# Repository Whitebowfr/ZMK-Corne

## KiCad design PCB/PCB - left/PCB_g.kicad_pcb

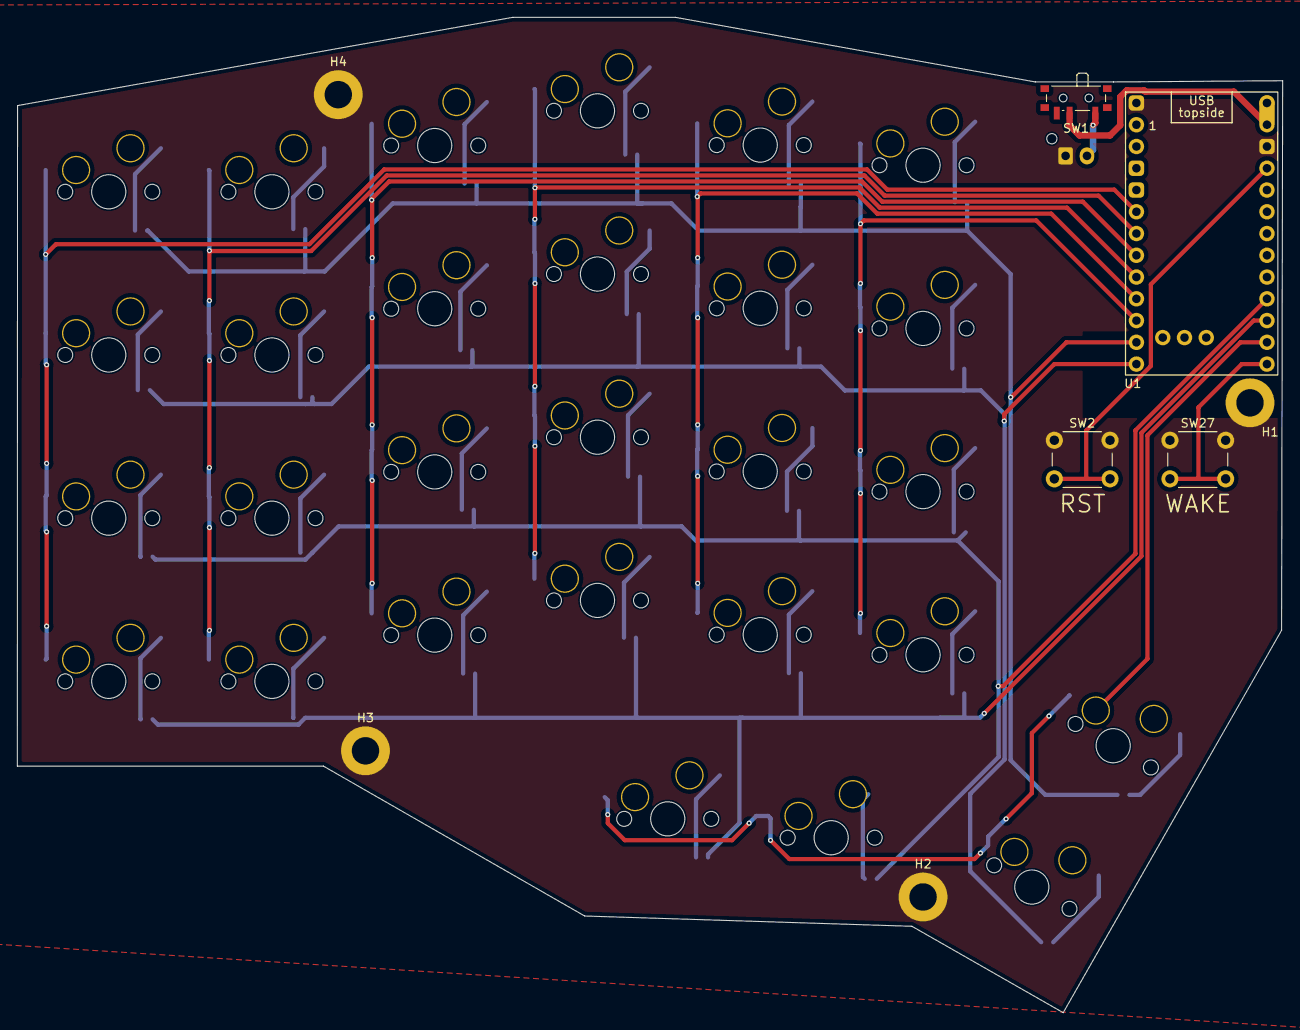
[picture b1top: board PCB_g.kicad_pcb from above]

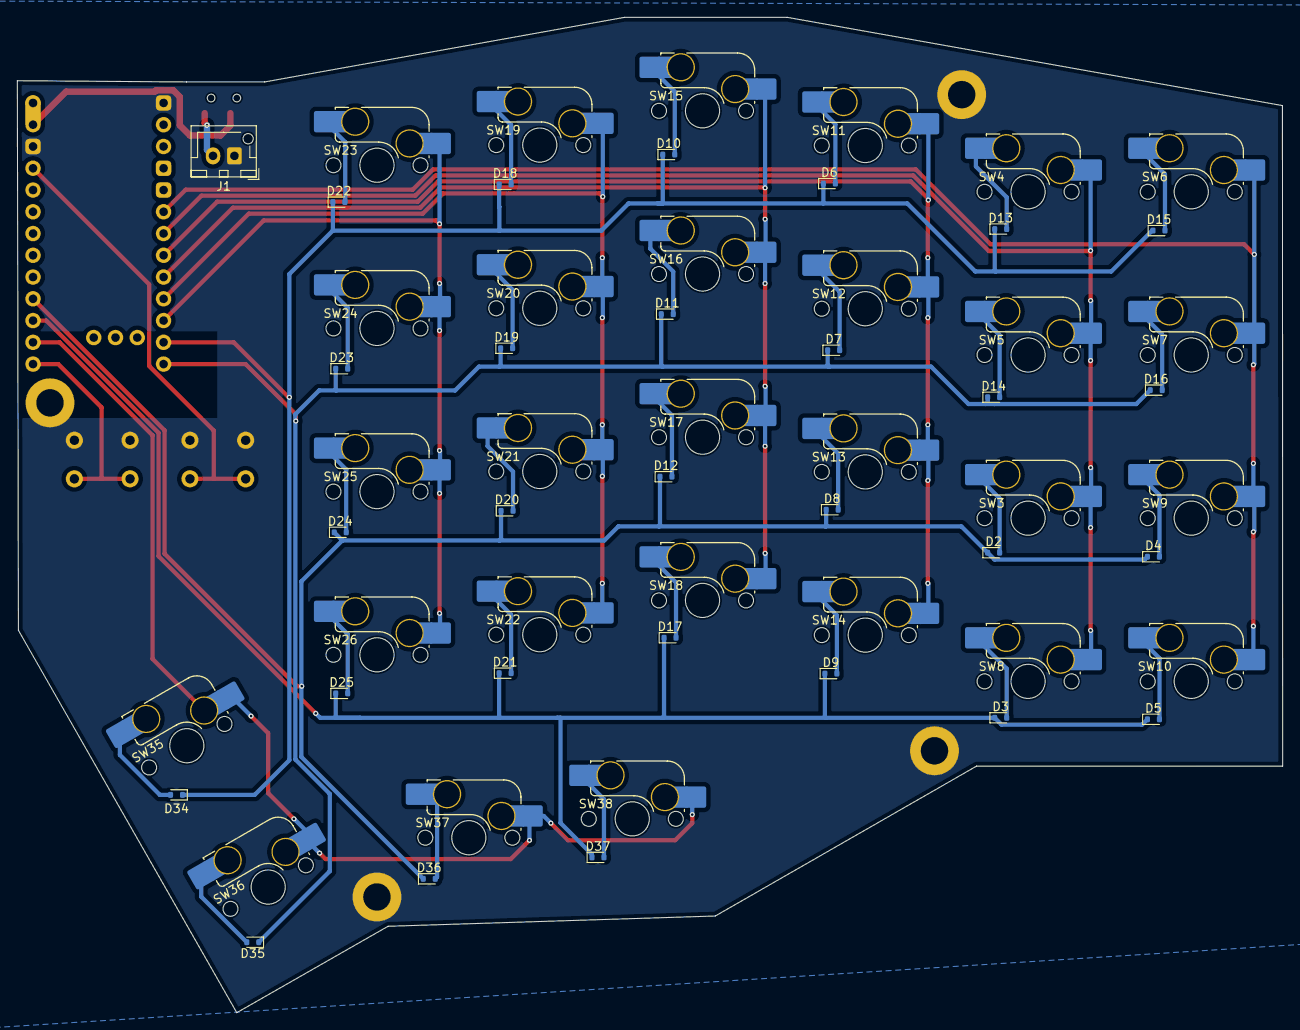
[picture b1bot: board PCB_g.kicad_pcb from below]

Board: 2 copper layers, 147.7 x 116.2 mm, 65 parts (57 on the bottom side), 44 nets.

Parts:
D2, D3, D4, D5, D6, D7, D8, D9, D10, D11, D12, D13, D14, D15, D16, D17, D18, D19, D20, D21, D22, D23, D24, D25, D34, D35, D36, D37: 1N4148WT; D_SOD-523
H1, H2, H3, H4: MountingHole_Pad; MountingHole_3.2mm_M3_ISO7380_Pad
J1: Conn_01x02; JST_XH_B2B-XH-AM_1x02_P2.50mm_Vertical
SW1: SW_SPDT; SW_SPDT_PCM12
SW2, SW27: SW_Push; SW_PUSH_6mm_H5mm
SW3, SW4, SW5, SW6, SW7, SW8, SW9, SW10, SW11, SW12, SW13, SW14, SW15, SW16, SW17, SW18, SW19, SW20, SW21, SW22, SW23, SW24, SW25, SW26, SW35, SW36, SW37, SW38: MX_SW_HS; SW_MX_HS_CPG151101S11_1u
U1: SuperMini nRF52840; SuperMini_nRF52840_AH_USBup

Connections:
+BATT: J1.2, SW1.1 (A)
GND: H1.1, H2.1, H3.1, H4.1, J1.1, SW2.1, SW27.1, U1.14 (GND), U1.28 (GND)
unnamed: D2.2 (A), SW3.2
unnamed: D3.2 (A), SW8.2
unnamed: D4.2 (A), SW9.2
unnamed: D5.2 (A), SW10.2
unnamed: D6.2 (A), SW11.2
unnamed: D7.2 (A), SW12.2
unnamed: D8.2 (A), SW13.2
unnamed: D9.2 (A), SW14.2
unnamed: D10.2 (A), SW15.2
unnamed: D11.2 (A), SW16.2
unnamed: D12.2 (A), SW17.2
unnamed: D13.2 (A), SW4.2
unnamed: D14.2 (A), SW5.2
unnamed: D15.2 (A), SW6.2
unnamed: D16.2 (A), SW7.2
unnamed: D17.2 (A), SW18.2
unnamed: D18.2 (A), SW19.2
unnamed: D19.2 (A), SW20.2
unnamed: D20.2 (A), SW21.2
unnamed: D21.2 (A), SW22.2
unnamed: D22.2 (A), SW23.2
unnamed: D23.2 (A), SW24.2
unnamed: D24.2 (A), SW25.2
unnamed: D25.2 (A), SW26.2
unnamed: D34.2 (A), SW35.2
unnamed: D35.2 (A), SW36.2
unnamed: D36.2 (A), SW37.2
unnamed: D37.2 (A), SW38.2
unnamed: SW1.2 (B), U1.13 (BAT+), U1.29 (BAT+)
RST: SW2.2, U1.15 (RST)
WAKE: SW27.2, U1.24 (P0.09-LF)
col0: SW3.1, SW4.1, SW5.1, SW8.1, U1.6 (P0.20)
col1: SW6.1, SW7.1, SW9.1, SW10.1, U1.5 (P0.17)
col2: SW11.1, SW12.1, SW13.1, SW14.1, U1.7 (P0.22)
col3: SW15.1, SW16.1, SW17.1, SW18.1, U1.8 (P0.24)
col4: SW35.1, SW36.1, SW37.1, SW38.1, U1.23 (P0.10-LF)
col5: SW19.1, SW20.1, SW21.1, SW22.1, U1.9 (P1.00)
col6: SW23.1, SW24.1, SW25.1, SW26.1, U1.10 (P0.11)
row0: D6.1 (K), D10.1 (K), D13.1 (K), D15.1 (K), D18.1 (K), D22.1 (K), D34.1 (K), U1.11 (P1.04-LF)
row1: D7.1 (K), D11.1 (K), D14.1 (K), D16.1 (K), D19.1 (K), D23.1 (K), D35.1 (K), U1.12 (P1.06-LF)
row2: D2.1 (K), D4.1 (K), D8.1 (K), D12.1 (K), D20.1 (K), D24.1 (K), D36.1 (K), U1.21 (P1.13-LF)
row3: D3.1 (K), D5.1 (K), D9.1 (K), D17.1 (K), D21.1 (K), D25.1 (K), D37.1 (K), U1.22 (P1.11-LF)

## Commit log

2025-02-28 Removed useless configs
2025-02-28 Switched column
2025-02-28 Swapped matrix
2025-02-28 Fixed columns
2025-02-28 Fixed thumb cluster
2025-03-01 Added studio and fixed arrows
2025-03-01 Added physical layout
2025-03-01 Removed typo
2025-03-10 Added 3D model, added reset firmware
2025-03-10 Used internal oscillator
2025-03-10 Swapped central peripheral
2025-03-11 Changed default keymap to better one
2025-03-11 Fixed bluetooth
2025-03-21 Tried upping the TX power and internal osc
2025-03-21 Tried upping the TX power and internal osc ag
2025-03-21 Tried upping the TX power and internal osc again
2025-09-05 Fixed dtsi inclusion
2025-09-05 Fixed name
2025-09-05 Fixed GPIOs
2025-09-05 Tried fixing connection issues
2025-09-08 Removed ZMK lock
